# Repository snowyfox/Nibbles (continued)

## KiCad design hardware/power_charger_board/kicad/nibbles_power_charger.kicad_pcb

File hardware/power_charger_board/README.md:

# Power board + charger (one board)

A copy of the [power board](../power_board/README.md) with the
[charger board](../charger_board/README.md) added, for laying both out as
**one board**. Made 2026-10-26 from the power board as it stood (one-sheet
schematic, placement and routing so far) and the charger board's 54 x 30 mm
placement. Open `kicad/nibbles_power_charger.kicad_pro`. The two
original projects are unchanged; this one is edited by hand in KiCad.

- Schematic: one sheet, the power board's sections with the charger below
  them as section 4. Shared nets keep their names (DOCK_VIN, PACK_F, GND,
  +3V3, +5V, PWR_SDA/SCL/INT), so they're one net across both.
- The XT30s that linked the two boards are gone: J10 and J11 on the power
  side, J21 and J22 on the charger side. DOCK_VIN and PACK_F now reach the
  charger through copper on this board. The JST-GH I2C link (J12 and J23)
  is gone too (2026-10-27).
- PCB: one outline, about 30.2 x 100 mm. The charger section (2026-10-27) is
  a copy of [KXUSBC2](https://github.com/manuelkasper/kxusbc2)'s BQ25792 layout (cloned at
  /Volumes/Code/kxusbc2): its placement, tracks, vias and zones, rotated
  -90 degrees with U2 at (45.25, 132.4), KX-only parts dropped. Built and
  checked first in `../power_charger_kx_test/`; the scripts that did it are
  in `../power_charger_kx_test/scripts/`. Parts KX doesn't have (R14 CE,
  R15 + LED1 STAT, R37/R38 ILIM, J4 NTC) are parked right of the board, and
  VAC1/VAC2 still need a link to DOCK_VIN.
- Assembly: power, thermal-pad and fine-pitch parts on top (hot plate);
  small 0402/0603 passives may go on the bottom (hot air, after the top).
  R10-R13 and C28 are 0402 to match KX's pads. Minimums relaxed to KX's
  JLCPCB values: via 0.45 mm, annular 0.075, hole clearance and hole to
  hole 0.2.
- Test points: TP1 (GND) and TP2 (TS) 2.5 mm pads by the charger, and
  TP3-TP24, 1.5 mm pads on the bottom, parked right of the board for
  placing: GND x2, DOCK_RAW, DOCK_VIN, PACK_F, LIGHT_BUS, LIGHT_OUT, +5V,
  +3V3, SYS, PMID, REGN, EFUSE_IMON, CHG_ILIM, EFUSE_PG, EFUSE_EN,
  GATE_DOCK/PACK/LEMO, CHG_QON, DOCK_DET, DOCK_UART.
- Dock input snubber R39 (2 ohm) + C49/C50 (1 uF 50 V) on DOCK_RAW, parked
  left of the board; place it at J2.
- **4 copper layers** for the whole board (one stackup per file, and the
  charger needs its inner ground plane). The power board's net class
  widths were worked out for 2 oz outer copper on 2 layers; recheck them
  for the stackup this board is ordered with. Ground pours on In1, In2
  (charger) and the whole bottom; the XT30 grounds and the SO-8FL drain tabs
  (Q5, Q6, Q9) connect solid, not with spokes.
- Connectors: all JST-GH vertical (7.3 mm mated, under the 9.9 mm caps).
  J4 NTC and J7 LEMO data/detect (BM02B-GHS-TBT), J8 dock LED (GH2),
  J9 I2C port 1 (keypad) and J11 I2C port 2 (pole segment), same GH6
  pinout, and J10 (GH8): a cable to the 3.49 instead of the J6 headers,
  1 +5V_349, 2 GND, 3 +3V3, 4 SDA, 5 SCL, 6 INT, 7 DOCK_UART, 8 DOCK_DET.
  Each connector's job is on the silkscreen; J7's signals' ground comes
  back on J2's XT30 ground, in the same LEMO cable.
- Mounting: H1/H2 (M2.5) on the 3.49's USB-end corner holes, H3 at
  (38.5, 118.5); the XT30 end has no room. Board name and rev on the
  bottom silkscreen.
- J6 is the stacking header for the base's Waveshare ESP32-S3-Touch-LCD-3.49,
  two 1x11 2.54 mm rows matching the 3.49's own J6 (row A) and J3 (row B),
  footprint `nibbles:Waveshare_ESP32-S3-Touch-LCD-3.49_Headers`. This
  board's top faces the 3.49's flat battery side (3 switches, where its
  header pins come out), with its screen facing up (corrected 2026-10-27).
  Rows 26.491 mm apart, its PCB 29.0 x 92.5 mm; outline and all its holes
  (4x 2.72 corners, 2x 1.6, 1x 2.4, from Waveshare's STEP) on User.Drawings.
  The STEP is the footprint's 3D model, 11 mm up (8.5 mm female header plus
  the male header's plastic): put it at
  `kicad/3d/ESP32-S3-Touch-LCD-3.49.step` (git-ignored, 40 MB; from Waveshare's
  CAD download for the board).
  - A2/A3/A4 = IO1/IO2/IO3: PWR_SDA, PWR_SCL, PWR_INT. A6 = IO5: DOCK_DET.
    B6 = IO44 (U0RXD; the base's console is on USB): DOCK_UART.
  - A11 = the 3.49's 5V, which is its USB-C VBUS: fed from +5V through D5
    (SS34) so the buck can't push current into a computer on its USB port.
  - A10/B10 = its 3V3 out (+3V3 here), A9/B9 GND. Everything else is left
    open: IO47/48 are its own I2C bus (QMI8658 at 0x6B and TCA9554 at 0x20
    clash with the BQ25798 and U8), IO38-41 its SD card, IO19/20 USB, IO0
    BOOT, IO4 its battery ADC, BAT its battery.
- Net classes: the power board's (Power 5 mm, Supply 1 mm) plus Charger
  3 mm (vias 0.8/0.4) on PMID, SYS, SW1 and SW2.

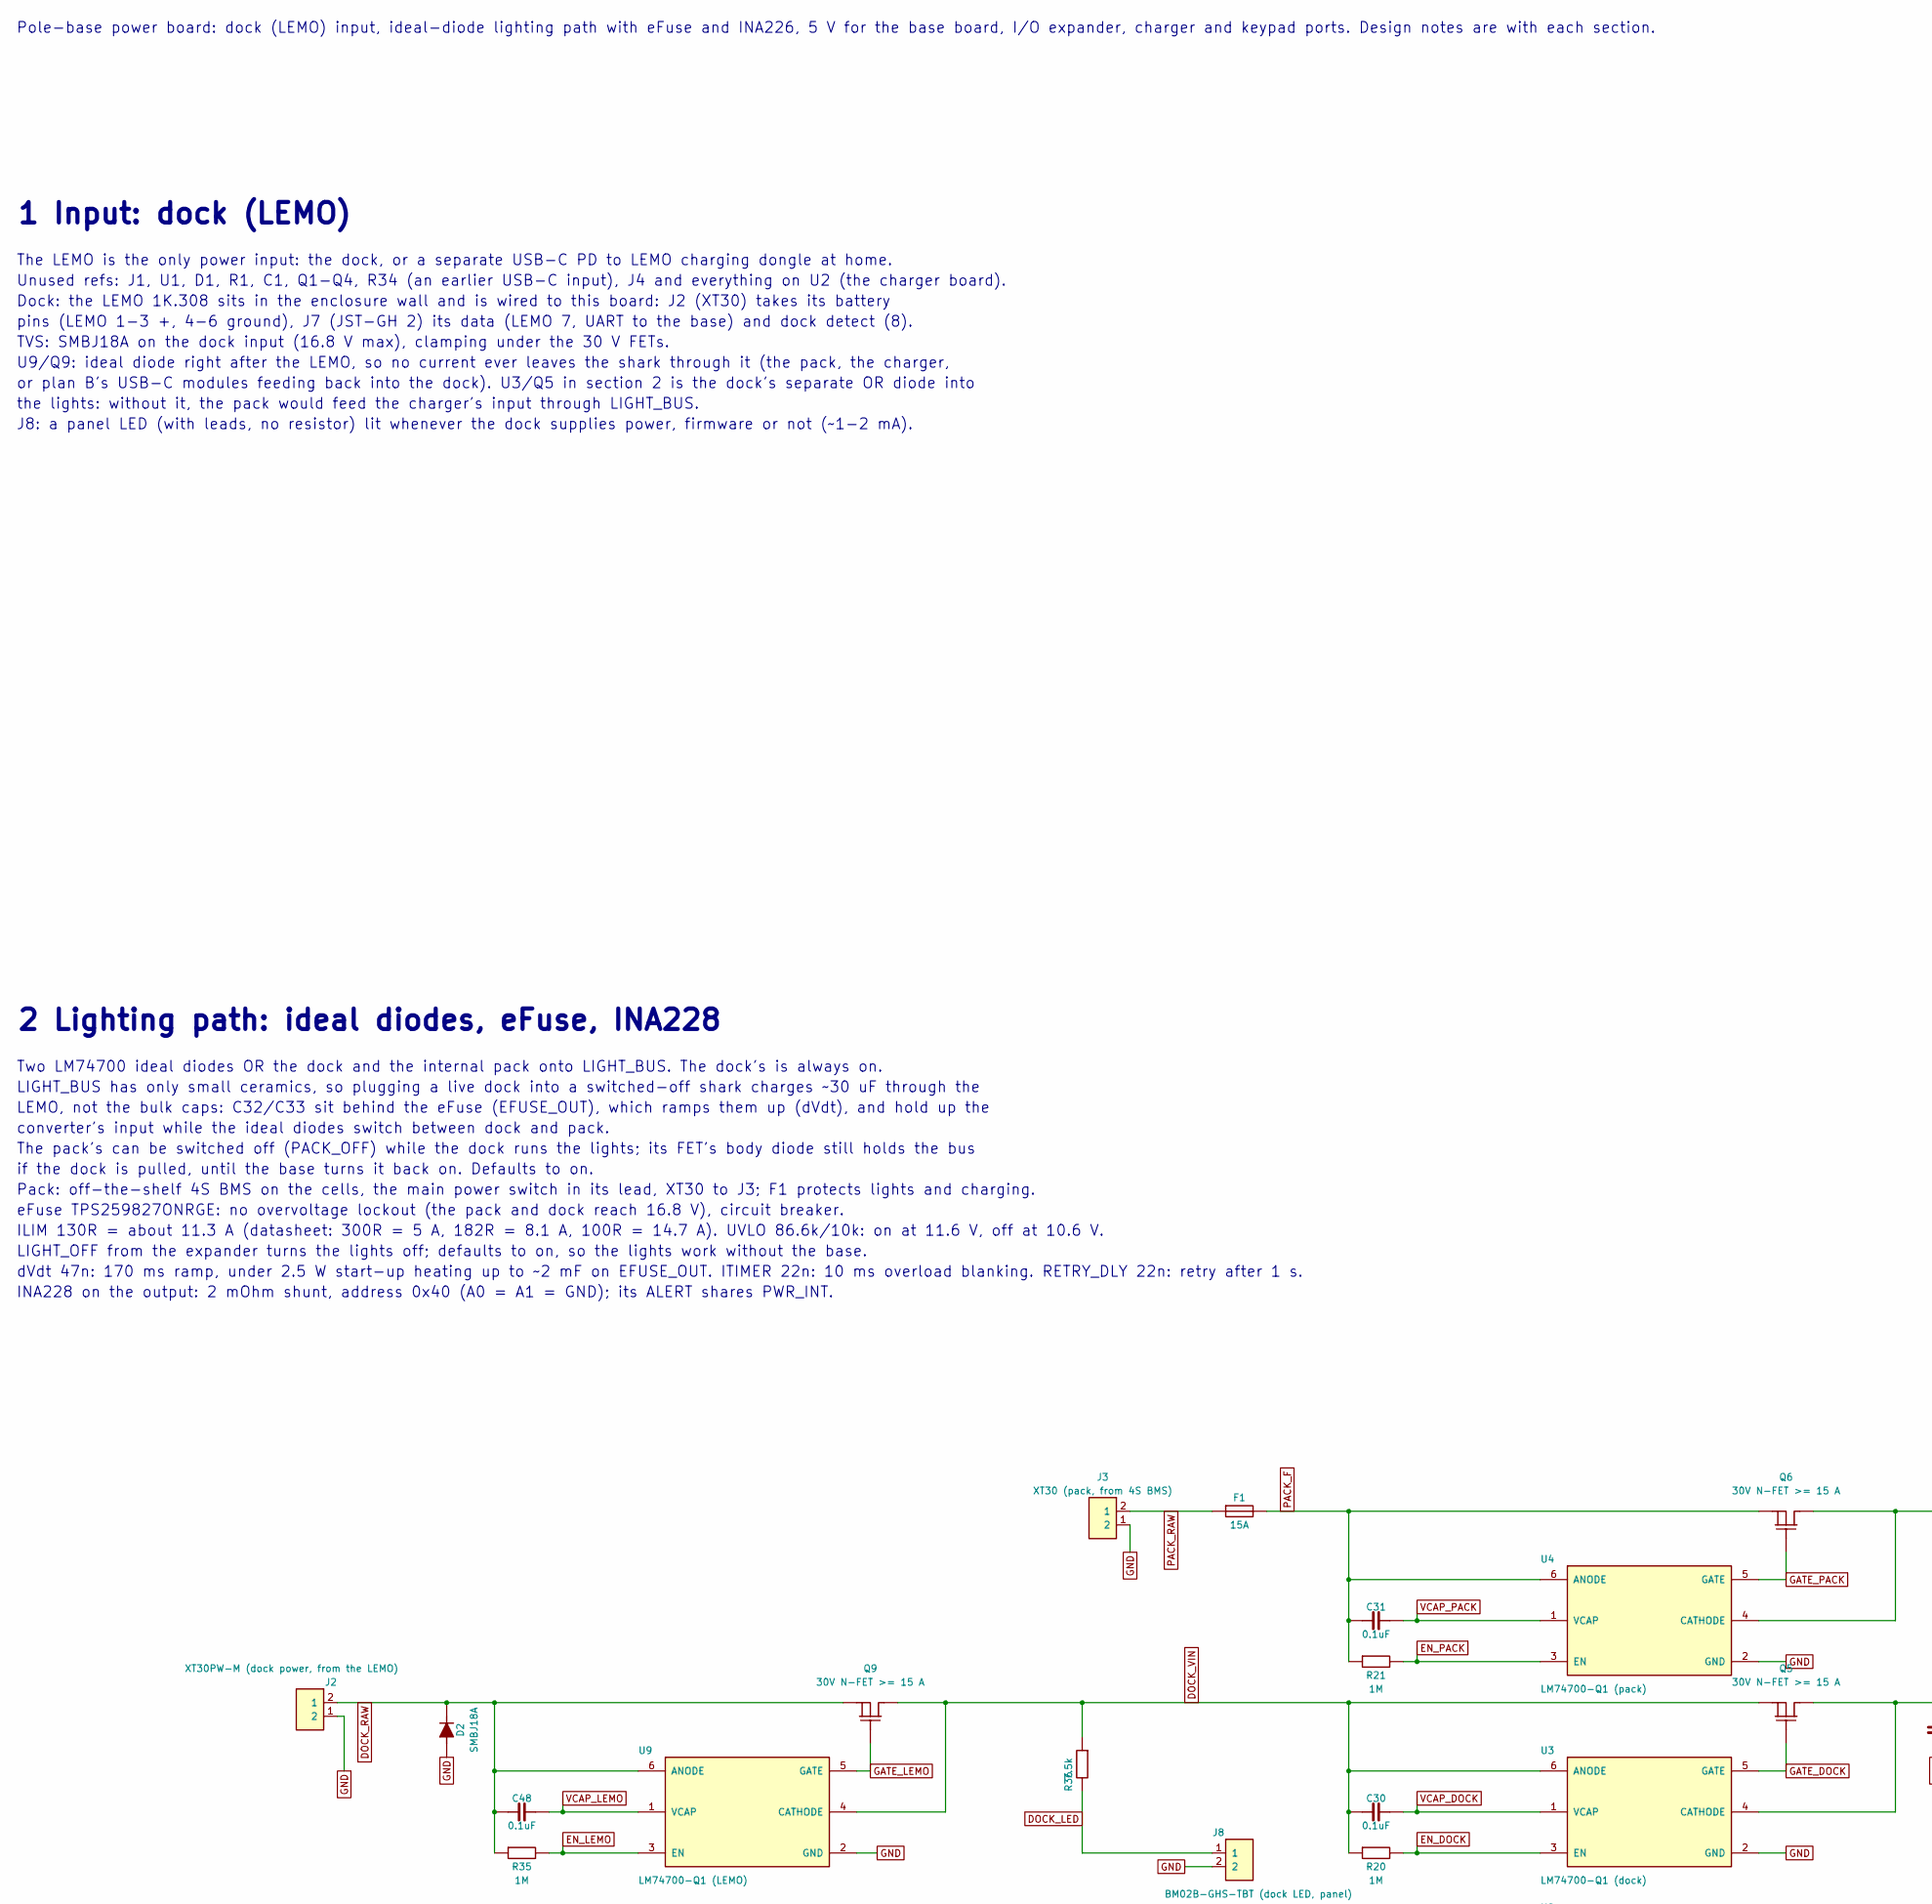
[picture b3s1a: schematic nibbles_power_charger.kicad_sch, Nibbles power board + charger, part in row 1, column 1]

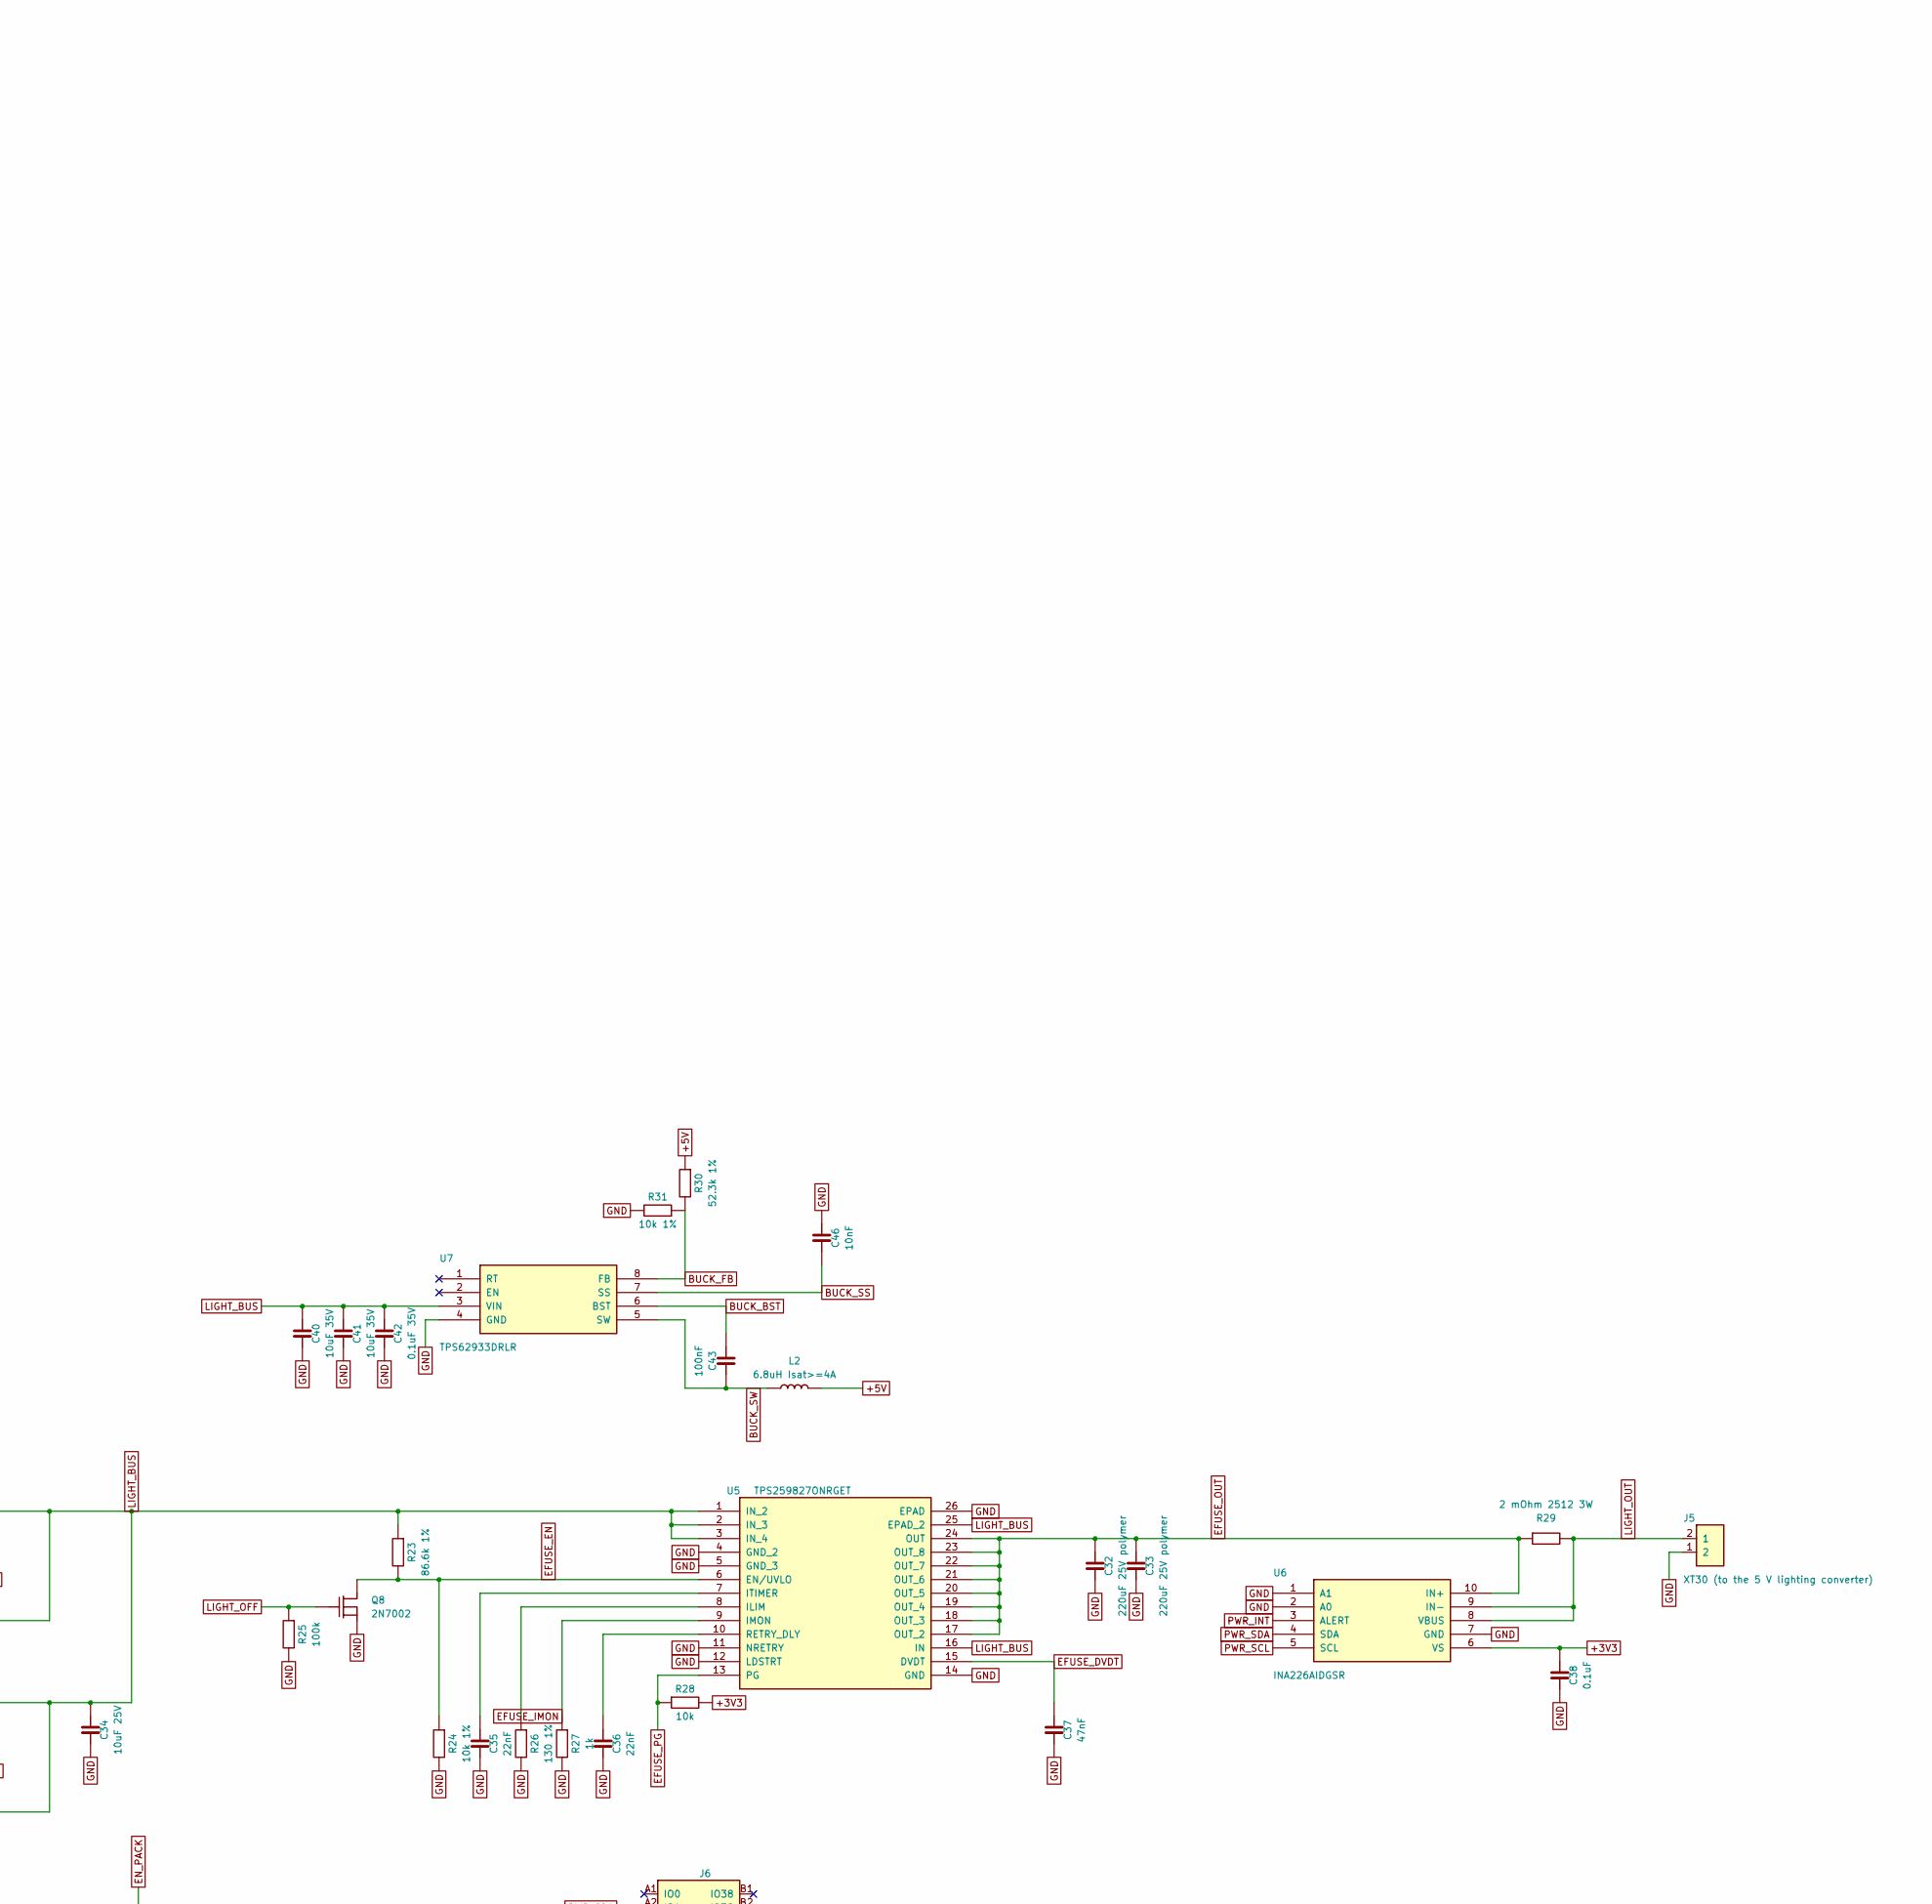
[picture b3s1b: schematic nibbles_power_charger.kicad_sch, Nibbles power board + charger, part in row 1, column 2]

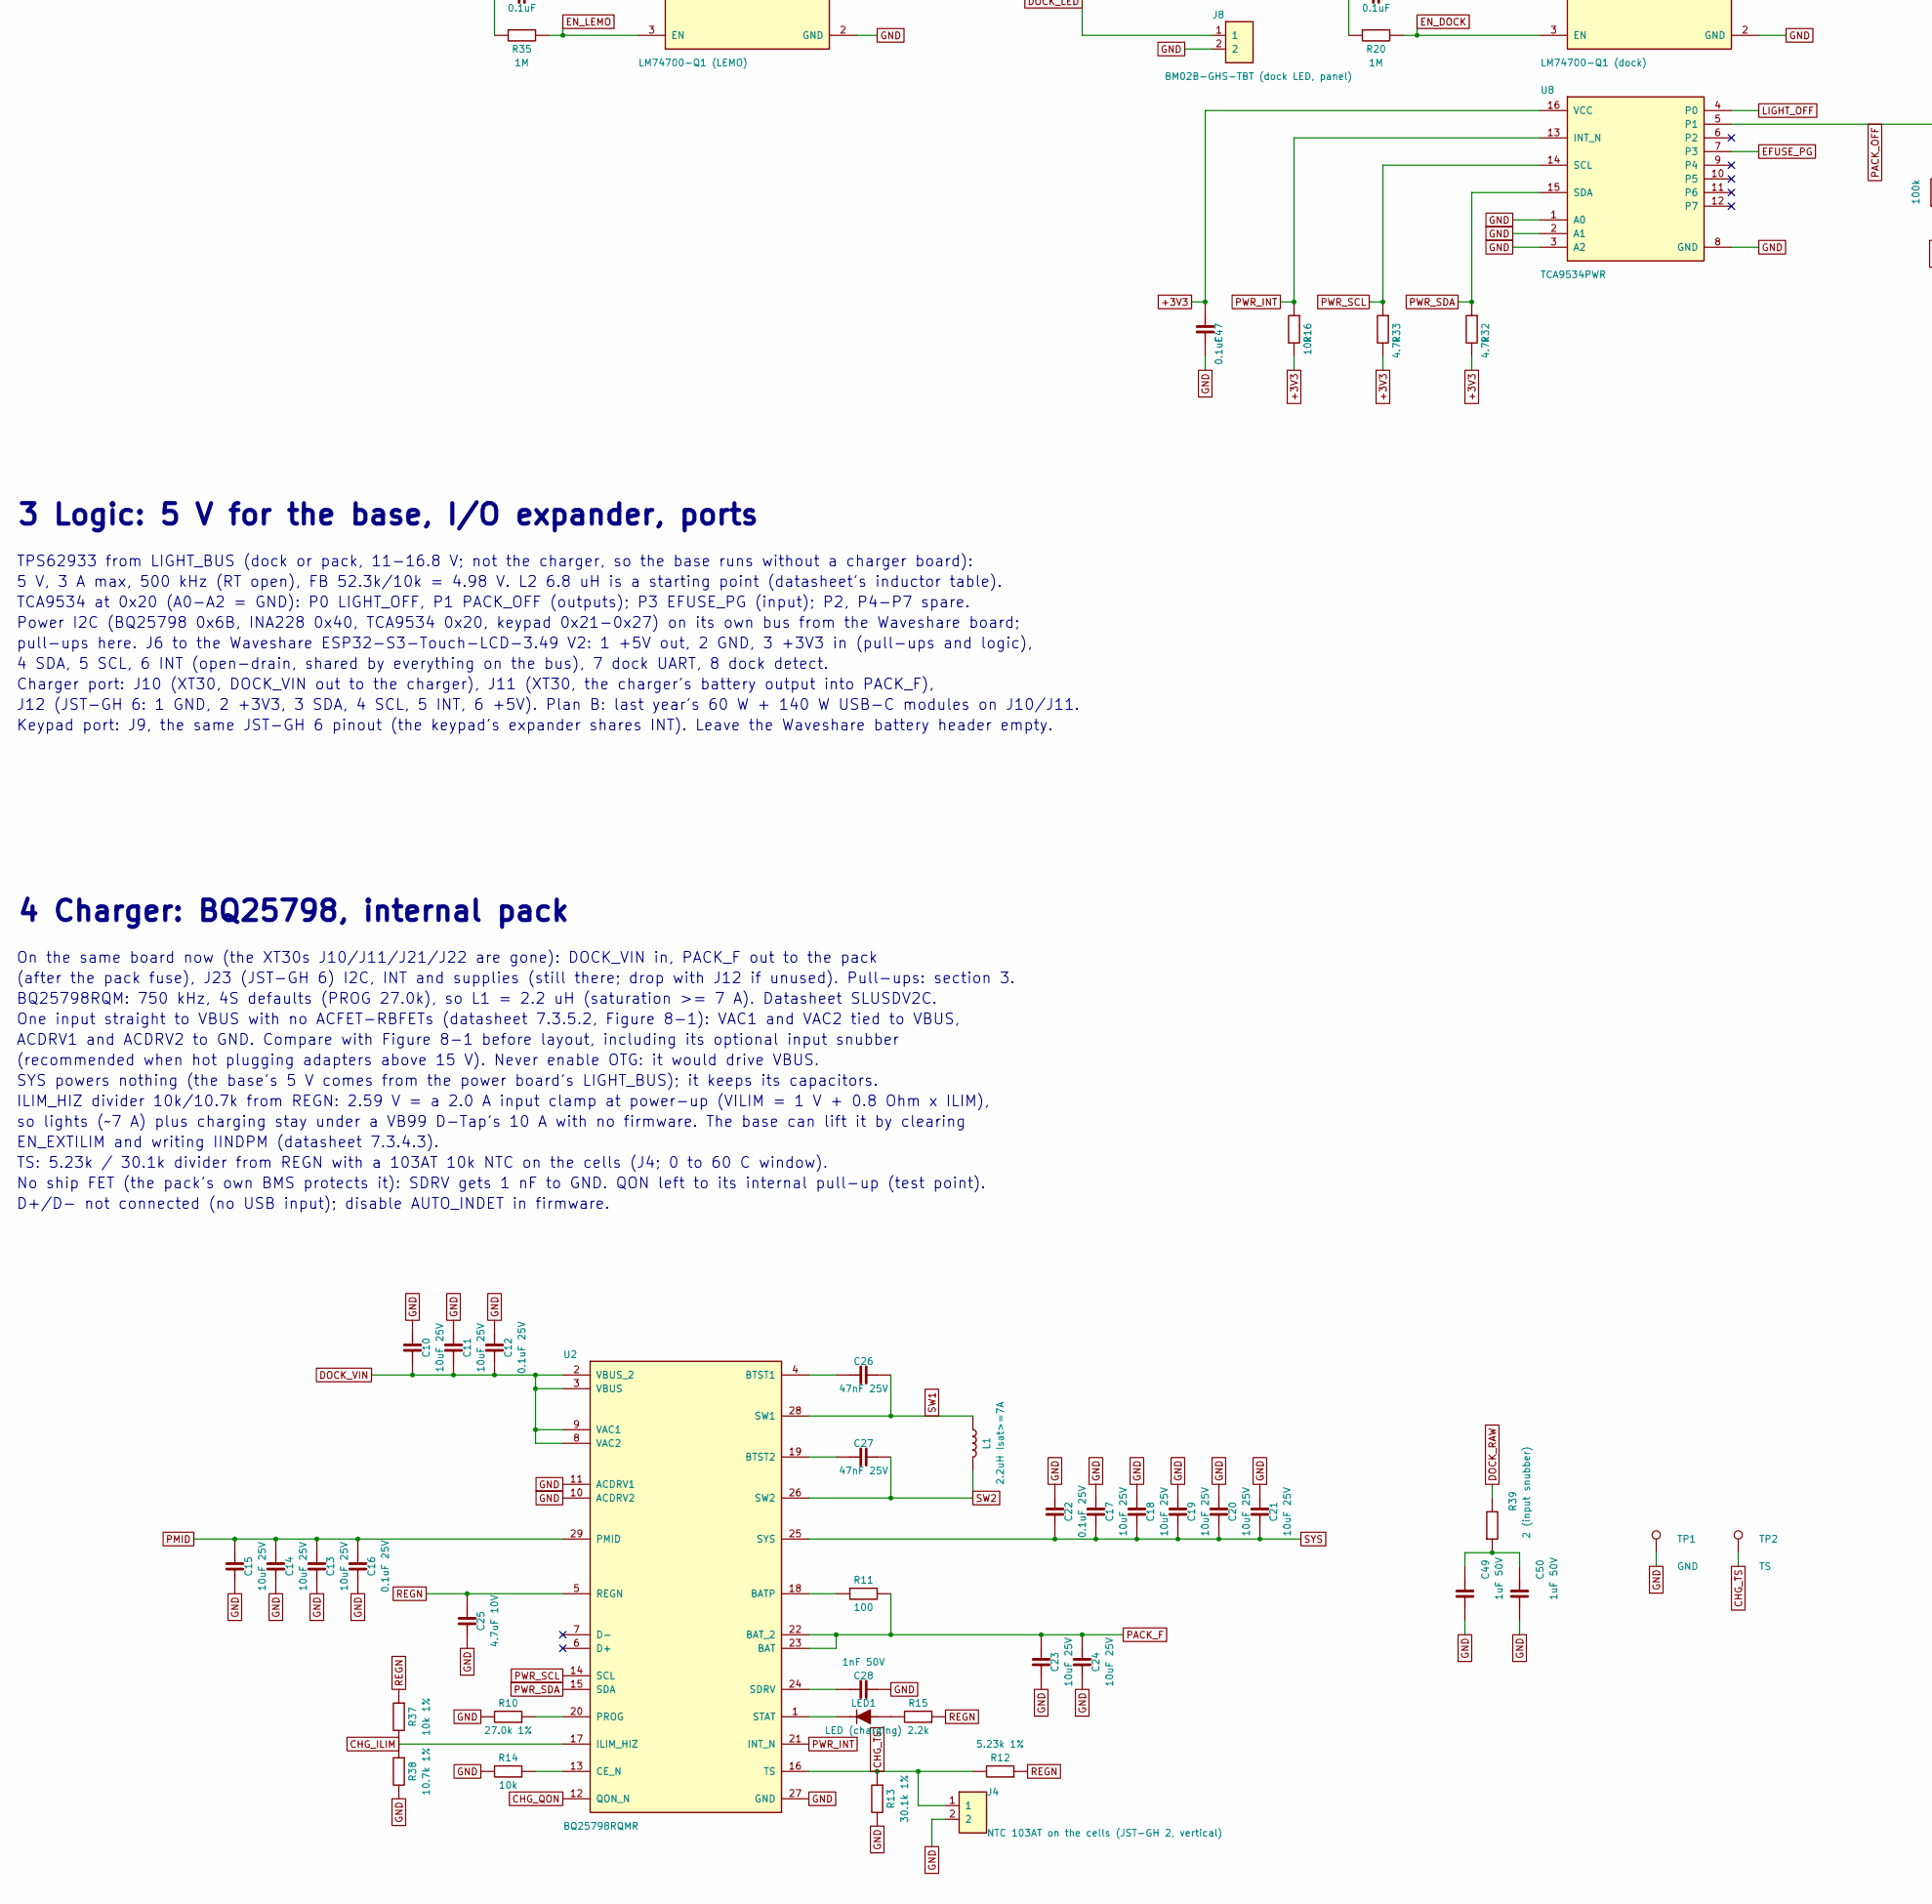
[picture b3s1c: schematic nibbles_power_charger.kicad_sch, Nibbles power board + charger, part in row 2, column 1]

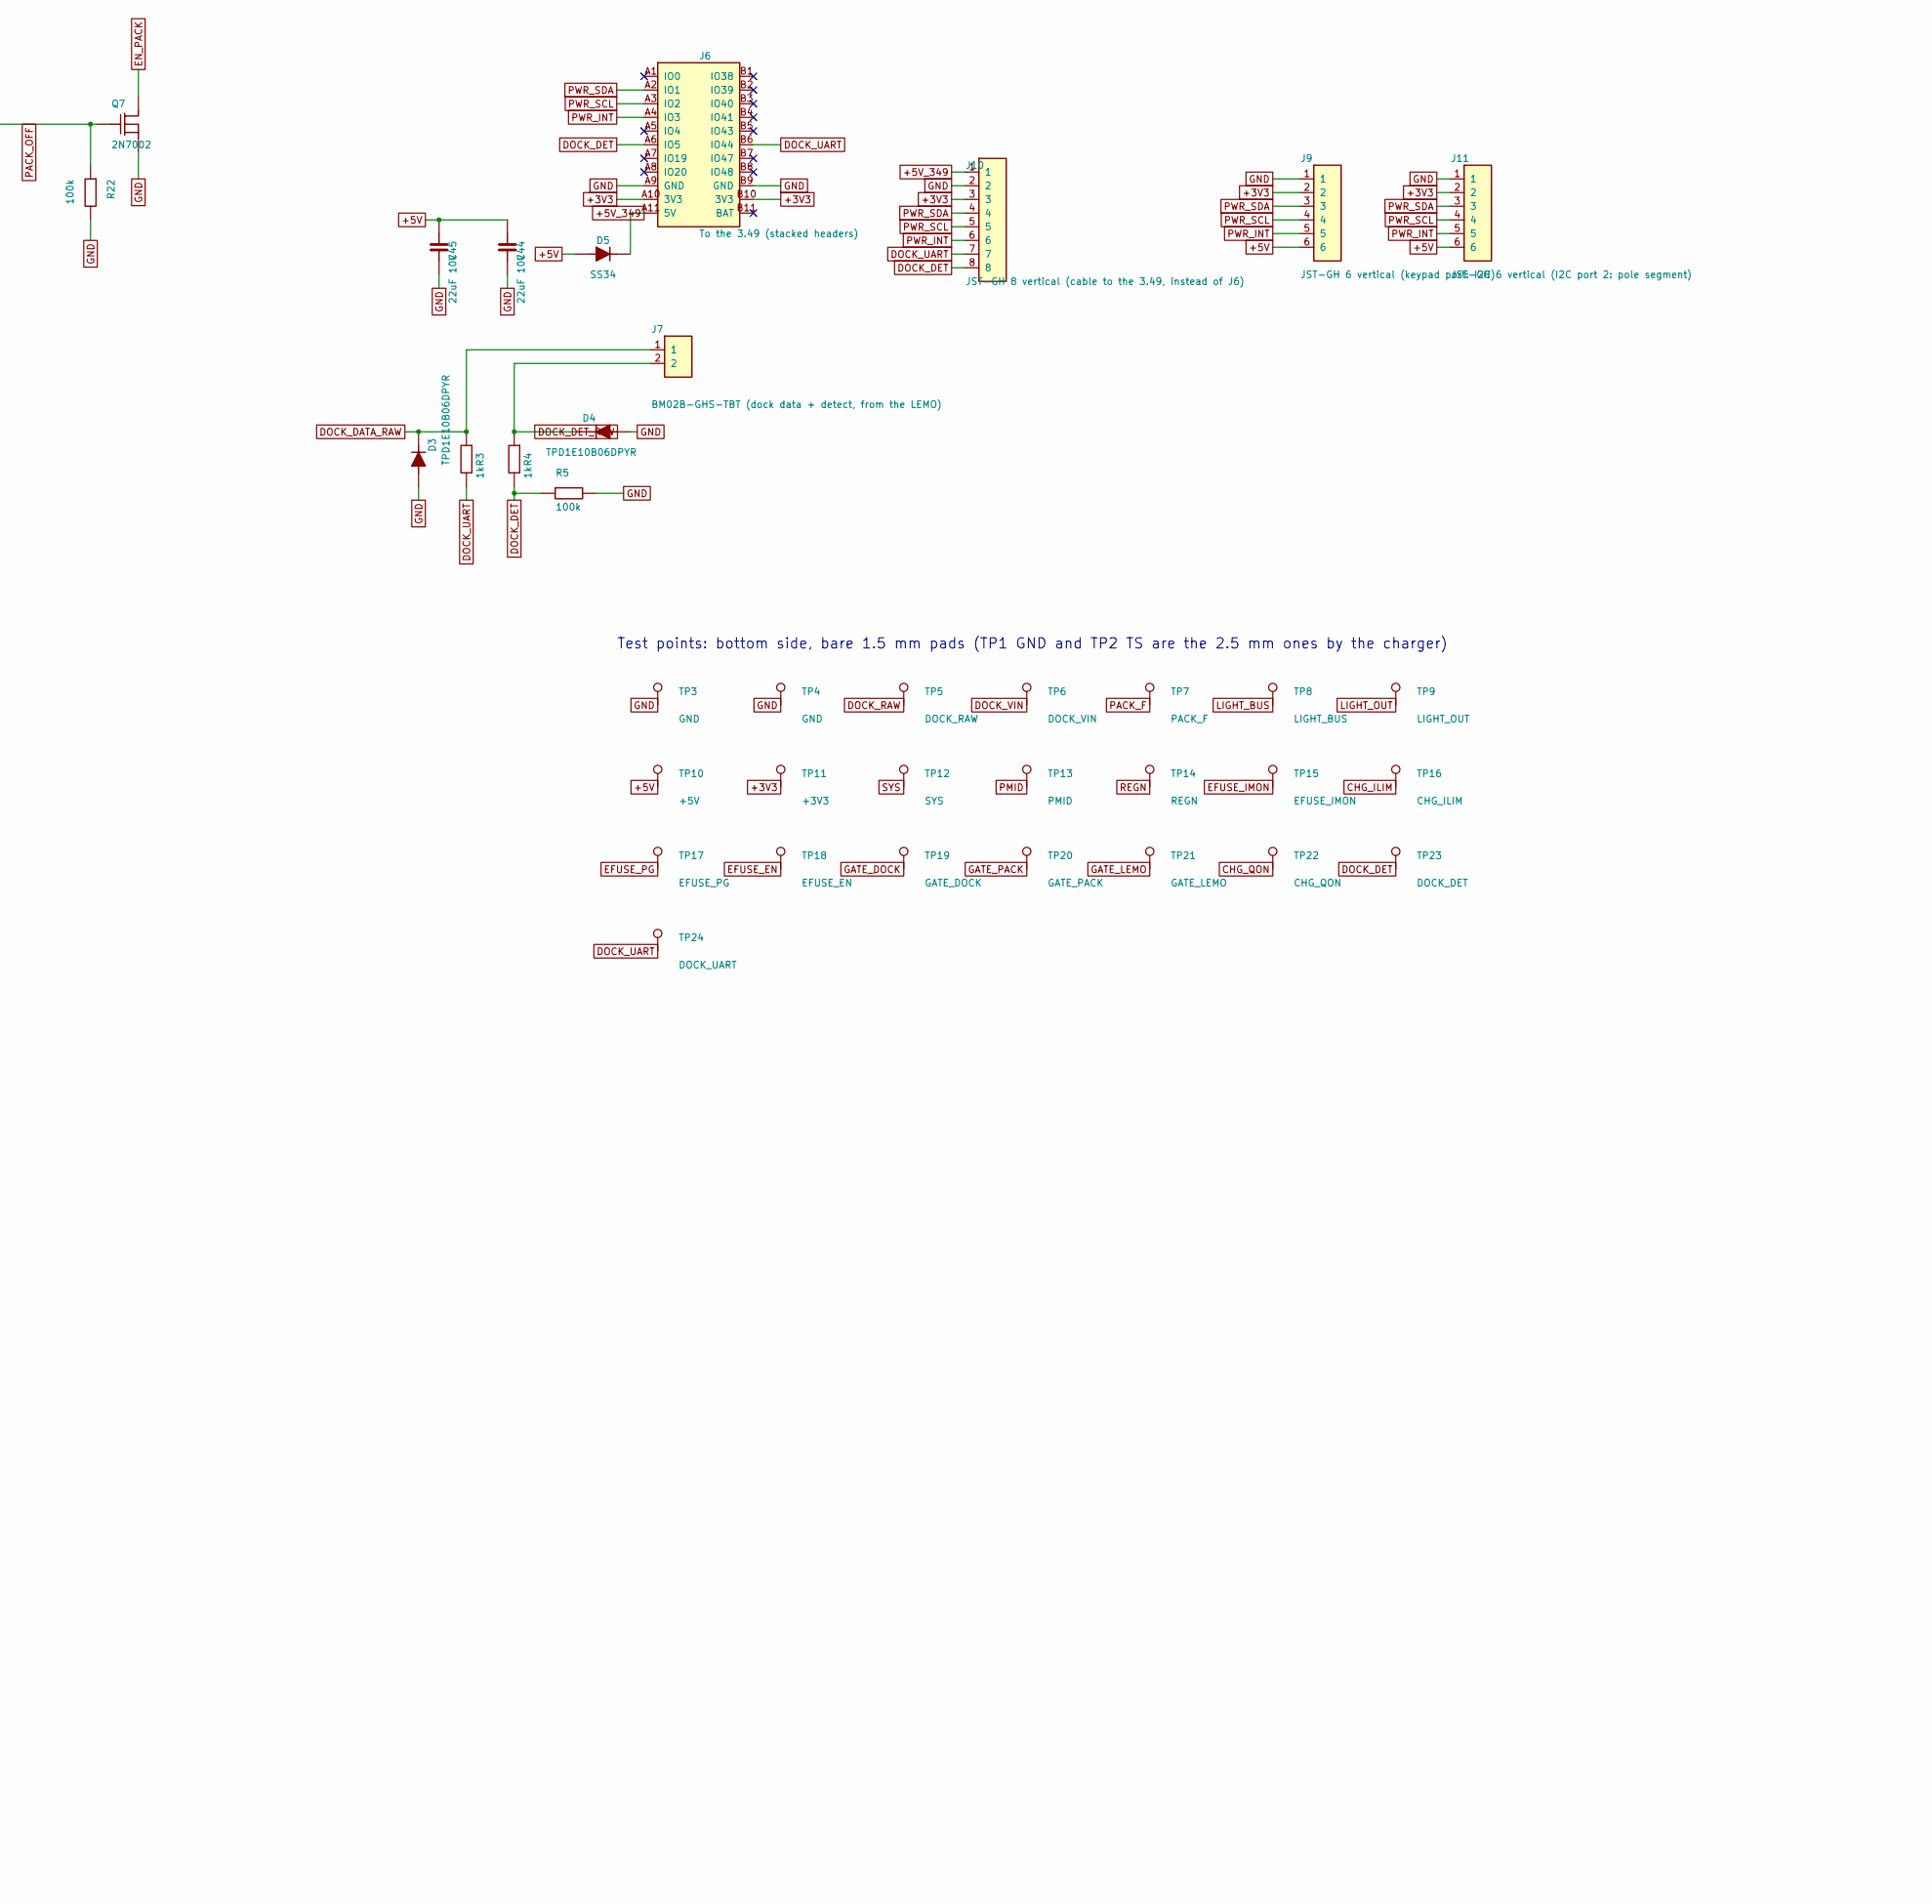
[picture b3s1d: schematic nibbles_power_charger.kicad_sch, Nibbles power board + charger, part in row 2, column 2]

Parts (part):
C10, C11, C13, C14, C15, C17, C18, C19, C20, C21, C23, C24, C34: 10uF 25V; C_0805_2012Metric; MPN CL21A106KAYNNNE; LCSC C15850
C12, C16, C22: 0.1uF 25V; C_0402_1005Metric; LCSC C131394
C25: 4.7uF 10V; C_0603_1608Metric; LCSC C19666
C26, C27: 47nF 25V; C_0603_1608Metric; LCSC C1622
C28: 1nF 50V; C_0402_1005Metric; LCSC C106205
C30, C31, C38, C47, C48: 0.1uF; C_0603_1608Metric; LCSC C14663
C32, C33: 220uF 25V polymer; CP_Elec_6.3x9.9; MPN KNM2220UF149EC0051; LCSC C2981459
C35, C36: 22nF; C_0603_1608Metric; LCSC C21122
C37: 47nF; C_0603_1608Metric; LCSC C1622
C40, C41: 10uF 35V; C_1206_3216Metric; LCSC C89632
C42: 0.1uF 35V; C_0603_1608Metric; LCSC C14663
C43: 100nF; C_0603_1608Metric; LCSC C14663
C44, C45: 22uF 10V; C_0805_2012Metric; LCSC C45783
C46: 10nF; C_0603_1608Metric; LCSC C1589
C49, C50: 1uF 50V; C_0603_1608Metric; LCSC C15849
D2: SMBJ18A; D_SMB; MPN SMBJ18A; LCSC C10212
D3, D4: TPD1E10B06DPYR; D_0402_1005Metric; MPN TPD1E10B06DPYR; LCSC C48260
D5: SS34; D_SMA; MPN SS34; LCSC C8678
F1: 15A; Fuse_1206_3216Metric; MPN CC12H15A-TR; LCSC C2443310
J2: XT30PW-M (dock power, from the LEMO); AMASS_XT30PW-M_1x02_P2.50mm_Horizontal; MPN XT30PW-M; LCSC C431092
J3: XT30 (pack, from 4S BMS); AMASS_XT30PW-M_1x02_P2.50mm_Horizontal; MPN XT30PW-M; LCSC C431092
J4: NTC 103AT on the cells (JST-GH 2, vertical); JST_GH_BM02B-GHS-TBT_1x02-1MP_P1.25mm_Vertical; MPN BM02B-GHS-TBT; LCSC C161690
J5: XT30 (to the 5 V lighting converter); AMASS_XT30PW-M_1x02_P2.50mm_Horizontal; MPN XT30PW-M; LCSC C431092
J6: To the 3.49 (stacked headers); Waveshare_ESP32-S3-Touch-LCD-3.49_Headers; MPN 2x 1x11 female header, 2.54 mm; LCSC C2932674
J7: BM02B-GHS-TBT (dock data + detect, from the LEMO); JST_GH_BM02B-GHS-TBT_1x02-1MP_P1.25mm_Vertical; MPN BM02B-GHS-TBT; LCSC C161690
J8: BM02B-GHS-TBT (dock LED, panel); JST_GH_BM02B-GHS-TBT_1x02-1MP_P1.25mm_Vertical; MPN BM02B-GHS-TBT; LCSC C161690
J9: JST-GH 6 vertical (keypad port: I2C); JST_GH_BM06B-GHS-TBT_1x06-1MP_P1.25mm_Vertical; MPN BM06B-GHS-TBT; LCSC C189892
J10: JST-GH 8 vertical (cable to the 3.49, instead of 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; JST_GH_BM08B-GHS-TBT_1x08-1MP_P1.25mm_Vertical; MPN BM08B-GHS-TBT; LCSC C133062
J11: JST-GH 6 vertical (I2C port 2: pole segment); JST_GH_BM06B-GHS-TBT_1x06-1MP_P1.25mm_Vertical; MPN BM06B-GHS-TBT; LCSC C189892
L1: 2.2uH Isat>=7A; L_Sunlord_MWSA0603S; MPN MWSA0603S-2R2MT; LCSC C285810
L2: 6.8uH Isat>=4A; L_Sunlord_MWSA0603S; MPN MWSA0603S-6R8MT; LCSC C285805
LED1: LED (charging); LED_0603_1608Metric; MPN KT-0603R; LCSC C2286
Q5, Q6, Q9: 30V N-FET >= 15 A; ONSemi_SO-8FL_488AA; MPN NTMFS4C022NT1G; LCSC C179623
Q7, Q8: 2N7002; SOT-23; MPN 2N7002; LCSC C8545
R3, R4, R27: 1k; R_0603_1608Metric; LCSC C21190
R5, R22, R25: 100k; R_0603_1608Metric; LCSC C25803
R10: 27.0k 1%; R_0402_1005Metric; LCSC C25771
R11: 100; R_0402_1005Metric; LCSC C25076
R12: 5.23k 1%; R_0402_1005Metric; LCSC C2933105
R13: 30.1k 1%; R_0402_1005Metric; LCSC C2998131
R14, R16, R28: 10k; R_0603_1608Metric; LCSC C98220
R15: 2.2k; R_0603_1608Metric; LCSC C4190
R20, R21, R35: 1M; R_0603_1608Metric; LCSC C22935
R23: 86.6k 1%; R_0603_1608Metric; LCSC C23121
R24, R31, R37: 10k 1%; R_0603_1608Metric; LCSC C98220
R26: 130 1%; R_0603_1608Metric; LCSC C22796
R29: 2 mOhm 2512 3W; R_2512_6332Metric; MPN LR2512-23R002F4; LCSC C154685
R30: 52.3k 1%; R_0603_1608Metric; LCSC C2933235
R32, R33: 4.7k; R_0603_1608Metric; LCSC C23162
R36: 7.5k; R_0603_1608Metric; LCSC C23234
R38: 10.7k 1%; R_0603_1608Metric; LCSC C22857
R39: 2 (input snubber); R_0603_1608Metric; LCSC C22977
TP1: GND; TestPoint_Pad_2.5x2.5mm
TP2: TS; TestPoint_Pad_2.5x2.5mm
TP3, TP4: GND; TestPoint_Pad_D1.5mm
TP5: DOCK_RAW; TestPoint_Pad_D1.5mm
TP6: DOCK_VIN; TestPoint_Pad_D1.5mm
TP7: PACK_F; TestPoint_Pad_D1.5mm
TP8: LIGHT_BUS; TestPoint_Pad_D1.5mm
TP9: LIGHT_OUT; TestPoint_Pad_D1.5mm
TP10: +5V; TestPoint_Pad_D1.5mm
TP11: +3V3; TestPoint_Pad_D1.5mm
TP12: SYS; TestPoint_Pad_D1.5mm
TP13: PMID; TestPoint_Pad_D1.5mm
TP14: REGN; TestPoint_Pad_D1.5mm
TP15: EFUSE_IMON; TestPoint_Pad_D1.5mm
TP16: CHG_ILIM; TestPoint_Pad_D1.5mm
TP17: EFUSE_PG; TestPoint_Pad_D1.5mm
TP18: EFUSE_EN; TestPoint_Pad_D1.5mm
TP19: GATE_DOCK; TestPoint_Pad_D1.5mm
TP20: GATE_PACK; TestPoint_Pad_D1.5mm
TP21: GATE_LEMO; TestPoint_Pad_D1.5mm
TP22: CHG_QON; TestPoint_Pad_D1.5mm
TP23: DOCK_DET; TestPoint_Pad_D1.5mm
TP24: DOCK_UART; TestPoint_Pad_D1.5mm
U2: BQ25798RQMR; RQM0029A-MFG; MPN BQ25798RQMR; LCSC C2876593
U3: LM74700-Q1 (dock); DBV0006A_N; MPN LM74700QDBVRQ1; LCSC C2941042
U4: LM74700-Q1 (pack); DBV0006A_N; MPN LM74700QDBVRQ1; LCSC C2941042
U5: TPS259827ONRGET; RGE24_2P5XP85X1P45_TEX; MPN TPS259827ONRGET; LCSC C2155765
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
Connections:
+3V3: C38.1, C47.1, J6.A10 (3V3), J6.B10 (3V3), J9.2, J10.3, J11.2, R16.2, R28.2, R32.2, R33.2, TP11.1, U6.6 (VS), U8.16 (VCC)
+5V: C44.1, C45.1, D5.2 (A), J9.6, J11.6, L2.2, R30.1, TP10.1
+5V_349: D5.1 (C), J6.A11 (5V), J10.1
BUCK_BST: C43.1, U7.6 (BST)
BUCK_FB: R30.2, R31.1, U7.8 (FB)
BUCK_SS: C46.1, U7.7 (SS)
BUCK_SW: C43.2, L2.1, U7.5 (SW)
CHG_ILIM: R37.2, R38.1, TP16.1, U2.17 (ILIM_HIZ)
CHG_QON: TP22.1, U2.12 (QON_N)
CHG_TS: J4.1, R12.2, R13.1, TP2.1, U2.16 (TS)
DOCK_DATA_RAW: D3.1 (C), J7.1, R3.1
DOCK_DET: J6.A6 (IO5), J10.8, R4.2, R5.1, TP23.1
DOCK_DET_RAW: D4.1 (C), J7.2, R4.1
DOCK_LED: J8.1, R36.2
DOCK_RAW: C48.2, D2.1 (C), J2.2 (1), Q9.1 (S), Q9.2 (S), Q9.3 (S), R35.1, R39.2, TP5.1, U9.6 (ANODE)
DOCK_UART: J6.B6 (IO44), J10.7, R3.2, TP24.1
DOCK_VIN: C10.1, C11.1, C12.1, C30.2, Q5.1 (S), Q5.2 (S), Q5.3 (S), Q9.5 (D), R20.1, R36.1, TP6.1, U2.2 (VBUS_2), U2.3 (VBUS), U2.8 (VAC2), U2.9 (VAC1), U3.6 (ANODE), U9.4 (CATHODE)
EFUSE_DVDT: C37.1, U5.15 (DVDT)
EFUSE_EN: Q8.3 (D), R23.2, R24.1, TP18.1, U5.6 (EN/UVLO)
EFUSE_IMON: R27.1, TP15.1, U5.9 (IMON)
EFUSE_OUT: C32.1, C33.1, R29.1, U5.17 (OUT_2), U5.18 (OUT_3), U5.19 (OUT_4), U5.20 (OUT_5), U5.21 (OUT_6), U5.22 (OUT_7), U5.23 (OUT_8), U5.24 (OUT), U6.10 (IN+)
EFUSE_PG: R28.1, TP17.1, U5.13 (PG), U8.7 (P3)
EN_DOCK: R20.2, U3.3 (EN)
EN_LEMO: R35.2, U9.3 (EN)
EN_PACK: Q7.3 (D), R21.2, U4.3 (EN)
GATE_DOCK: Q5.4 (G), TP19.1, U3.5 (GATE)
GATE_LEMO: Q9.4 (G), TP21.1, U9.5 (GATE)
GATE_PACK: Q6.4 (G), TP20.1, U4.5 (GATE)
GND: C10.2, C11.2, C12.2, C13.2, C14.2, C15.2, C16.2, C17.2, C18.2, C19.2, C20.2, C21.2, C22.2, C23.2, C24.2, C25.2, C28.2, C32.2, C33.2, C34.2, C35.2, C36.2, C37.2, C38.2, C40.2, C41.2, C42.2, C44.2, C45.2, C46.2, C47.2, C49.1, C50.1, D2.2 (A), D3.2 (A), D4.2 (A), J2.1 (2), J3.1 (2), J4.2, J5.1 (2), J6.A9 (GND), J6.B9 (GND), J8.2, J9.1, J10.2, J11.1, Q7.2 (S), Q8.2 (S), R5.2, R10.2, R13.2, R14.2, R22.2, R24.2, R25.2, R26.2, R27.2, R31.2, R38.2, TP1.1, TP3.1, TP4.1, U2.10 (ACDRV2), U2.11 (ACDRV1), U2.27 (GND), U3.2 (GND), U4.2 (GND), U5.4 (GND_2), U5.5 (GND_3), U5.11 (NRETRY), U5.12 (LDSTRT), U5.14 (GND), U5.26 (EPAD), U6.1 (A1), U6.2 (A0), U6.7 (GND), U7.4 (GND), U8.1 (A0), U8.2 (A1), U8.3 (A2), U8.8 (GND), U9.2 (GND)
LIGHT_BUS: C34.1, C40.1, C41.1, C42.1, Q5.5 (D), Q6.5 (D), R23.1, TP8.1, U3.4 (CATHODE), U4.4 (CATHODE), U5.1 (IN_2), U5.2 (IN_3), U5.3 (IN_4), U5.16 (IN), U5.25 (EPAD_2), U7.3 (VIN)
LIGHT_OFF: Q8.1 (G), R25.1, U8.4 (P0)
LIGHT_OUT: J5.2 (1), R29.2, TP9.1, U6.8 (VBUS), U6.9 (IN-)
unnamed: C49.2, C50.2, R39.1
unnamed: LED1.2 (A), R15.2
unnamed: LED1.1 (C), U2.1 (STAT)
unnamed: R11.1, U2.18 (BATP)
unnamed: C26.1, U2.4 (BTST1)
unnamed: C27.1, U2.19 (BTST2)
unnamed: R14.1, U2.13 (CE_N)
unnamed: R10.1, U2.20 (PROG)
unnamed: C28.1, U2.24 (SDRV)
unnamed: R26.1, U5.8 (ILIM)
unnamed: C35.1, U5.7 (ITIMER)
unnamed: C36.1, U5.10 (RETRY_DLY)
PACK_F: C23.1, C24.1, C31.2, F1.2, Q6.1 (S), Q6.2 (S), Q6.3 (S), R11.2, R21.1, TP7.1, U2.22 (BAT_2), U2.23 (BAT), U4.6 (ANODE)
PACK_OFF: Q7.1 (G), R22.1, U8.5 (P1)
PACK_RAW: F1.1, J3.2 (1)
PMID: C13.1, C14.1, C15.1, C16.1, TP13.1, U2.29 (PMID)
PWR_INT: J6.A4 (IO3), J9.5, J10.6, J11.5, R16.1, U2.21 (INT_N), U6.3 (ALERT), U8.13 (INT_N)
PWR_SCL: J6.A3 (IO2), J9.4, J10.5, J11.4, R33.1, U2.14 (SCL), U6.5 (SCL), U8.14 (SCL)
PWR_SDA: J6.A2 (IO1), J9.3, J10.4, J11.3, R32.1, U2.15 (SDA), U6.4 (SDA), U8.15 (SDA)
REGN: C25.1, R12.1, R15.1, R37.1, TP14.1, U2.5 (REGN)
SW1: C26.2, L1.1, U2.28 (SW1)
SW2: C27.2, L1.2, U2.26 (SW2)
SYS: C17.1, C18.1, C19.1, C20.1, C21.1, C22.1, TP12.1, U2.25 (SYS)
VCAP_DOCK: C30.1, U3.1 (VCAP)
VCAP_LEMO: C48.1, U9.1 (VCAP)
VCAP_PACK: C31.1, U4.1 (VCAP)

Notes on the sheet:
LEMO, not the bulk caps: C32/C33 sit behind the eFuse (EFUSE_OUT), which ramps them up (dVdt), and hold up the
Pack: off-the-shelf 4S BMS on the cells, the main power switch in its lead, XT30 to J3; F1 protects lights and charging.
Pole-base power board: dock (LEMO) input, ideal-diode lighting path with eFuse and INA226, 5 V for the base board, I/O expander, charger and keypad ports. Design notes are with each section.
EN_EXTILIM and writing IINDPM (datasheet 7.3.4.3).
Power I2C (BQ25798 0x6B, INA228 0x40, TCA9534 0x20, keypad 0x21-0x27) on its own bus from the Waveshare board;
TS: 5.23k / 30.1k divider from REGN with a 103AT 10k NTC on the cells (J4; 0 to 60 C window).
eFuse TPS259827ONRGE: no overvoltage lockout (the pack and dock reach 16.8 V), circuit breaker.
or plan B's USB-C modules feeding back into the dock). U3/Q5 in section 2 is the dock's separate OR diode into
SYS powers nothing (the base's 5 V comes from the power board's LIGHT_BUS); it keeps its capacitors.
TPS62933 from LIGHT_BUS (dock or pack, 11-16.8 V; not the charger, so the base runs without a charger board):
if the dock is pulled, until the base turns it back on. Defaults to on.
U9/Q9: ideal diode right after the LEMO, so no current ever leaves the shark through it (the pack, the charger,
(recommended when hot plugging adapters above 15 V). Never enable OTG: it would drive VBUS.
5 V, 3 A max, 500 kHz (RT open), FB 52.3k/10k = 4.98 V. L2 6.8 uH is a starting point (datasheet's inductor table).
LIGHT_OFF from the expander turns the lights off; defaults to on, so the lights work without the base.
LIGHT_BUS has only small ceramics, so plugging a live dock into a switched-off shark charges ~30 uF through the
INA228 on the output: 2 mOhm shunt, address 0x40 (A0 = A1 = GND); its ALERT shares PWR_INT.
pull-ups here. J6 to the Waveshare ESP32-S3-Touch-LCD-3.49 V2: 1 +5V out, 2 GND, 3 +3V3 in (pull-ups and logic),
Test points: bottom side, bare 1.5 mm pads (TP1 GND and TP2 TS are the 2.5 mm ones by the charger)
D+/D- not connected (no USB input); disable AUTO_INDET in firmware.
2 Lighting path: ideal diodes, eFuse, INA228
1 Input: dock (LEMO)
4 Charger: BQ25798, internal pack
The LEMO is the only power input: the dock, or a separate USB-C PD to LEMO charging dongle at home.
On the same board now (the XT30s J10/J11/J21/J22 are gone): DOCK_VIN in, PACK_F out to the pack
Unused refs: J1, U1, D1, R1, C1, Q1-Q4, R34 (an earlier USB-C input), J4 and everything on U2 (the charger board).
(after the pack fuse), J23 (JST-GH 6) I2C, INT and supplies (still there; drop with J12 if unused). Pull-ups: section 3.
Two LM74700 ideal diodes OR the dock and the internal pack onto LIGHT_BUS. The dock's is always on.
J12 (JST-GH 6: 1 GND, 2 +3V3, 3 SDA, 4 SCL, 5 INT, 6 +5V). Plan B: last year's 60 W + 140 W USB-C modules on J10/J11.
Keypad port: J9, the same JST-GH 6 pinout (the keypad's expander shares INT). Leave the Waveshare battery header empty.
TVS: SMBJ18A on the dock input (16.8 V max), clamping under the 30 V FETs.
ACDRV1 and ACDRV2 to GND. Compare with Figure 8-1 before layout, including its optional input snubber
dVdt 47n: 170 ms ramp, under 2.5 W start-up heating up to ~2 mF on EFUSE_OUT. ITIMER 22n: 10 ms overload blanking. RETRY_DLY 22n: retry after 1 s.
J8: a panel LED (with leads, no resistor) lit whenever the dock supplies power, firmware or not (~1-2 mA).
so lights (~7 A) plus charging stay under a VB99 D-Tap's 10 A with no firmware. The base can lift it by clearing
3 Logic: 5 V for the base, I/O expander, ports
4 SDA, 5 SCL, 6 INT (open-drain, shared by everything on the bus), 7 dock UART, 8 dock detect.
Dock: the LEMO 1K.308 sits in the enclosure wall and is wired to this board: J2 (XT30) takes its battery
BQ25798RQM: 750 kHz, 4S defaults (PROG 27.0k), so L1 = 2.2 uH (saturation >= 7 A). Datasheet SLUSDV2C.
ILIM 130R = about 11.3 A (datasheet: 300R = 5 A, 182R = 8.1 A, 100R = 14.7 A). UVLO 86.6k/10k: on at 11.6 V, off at 10.6 V.
